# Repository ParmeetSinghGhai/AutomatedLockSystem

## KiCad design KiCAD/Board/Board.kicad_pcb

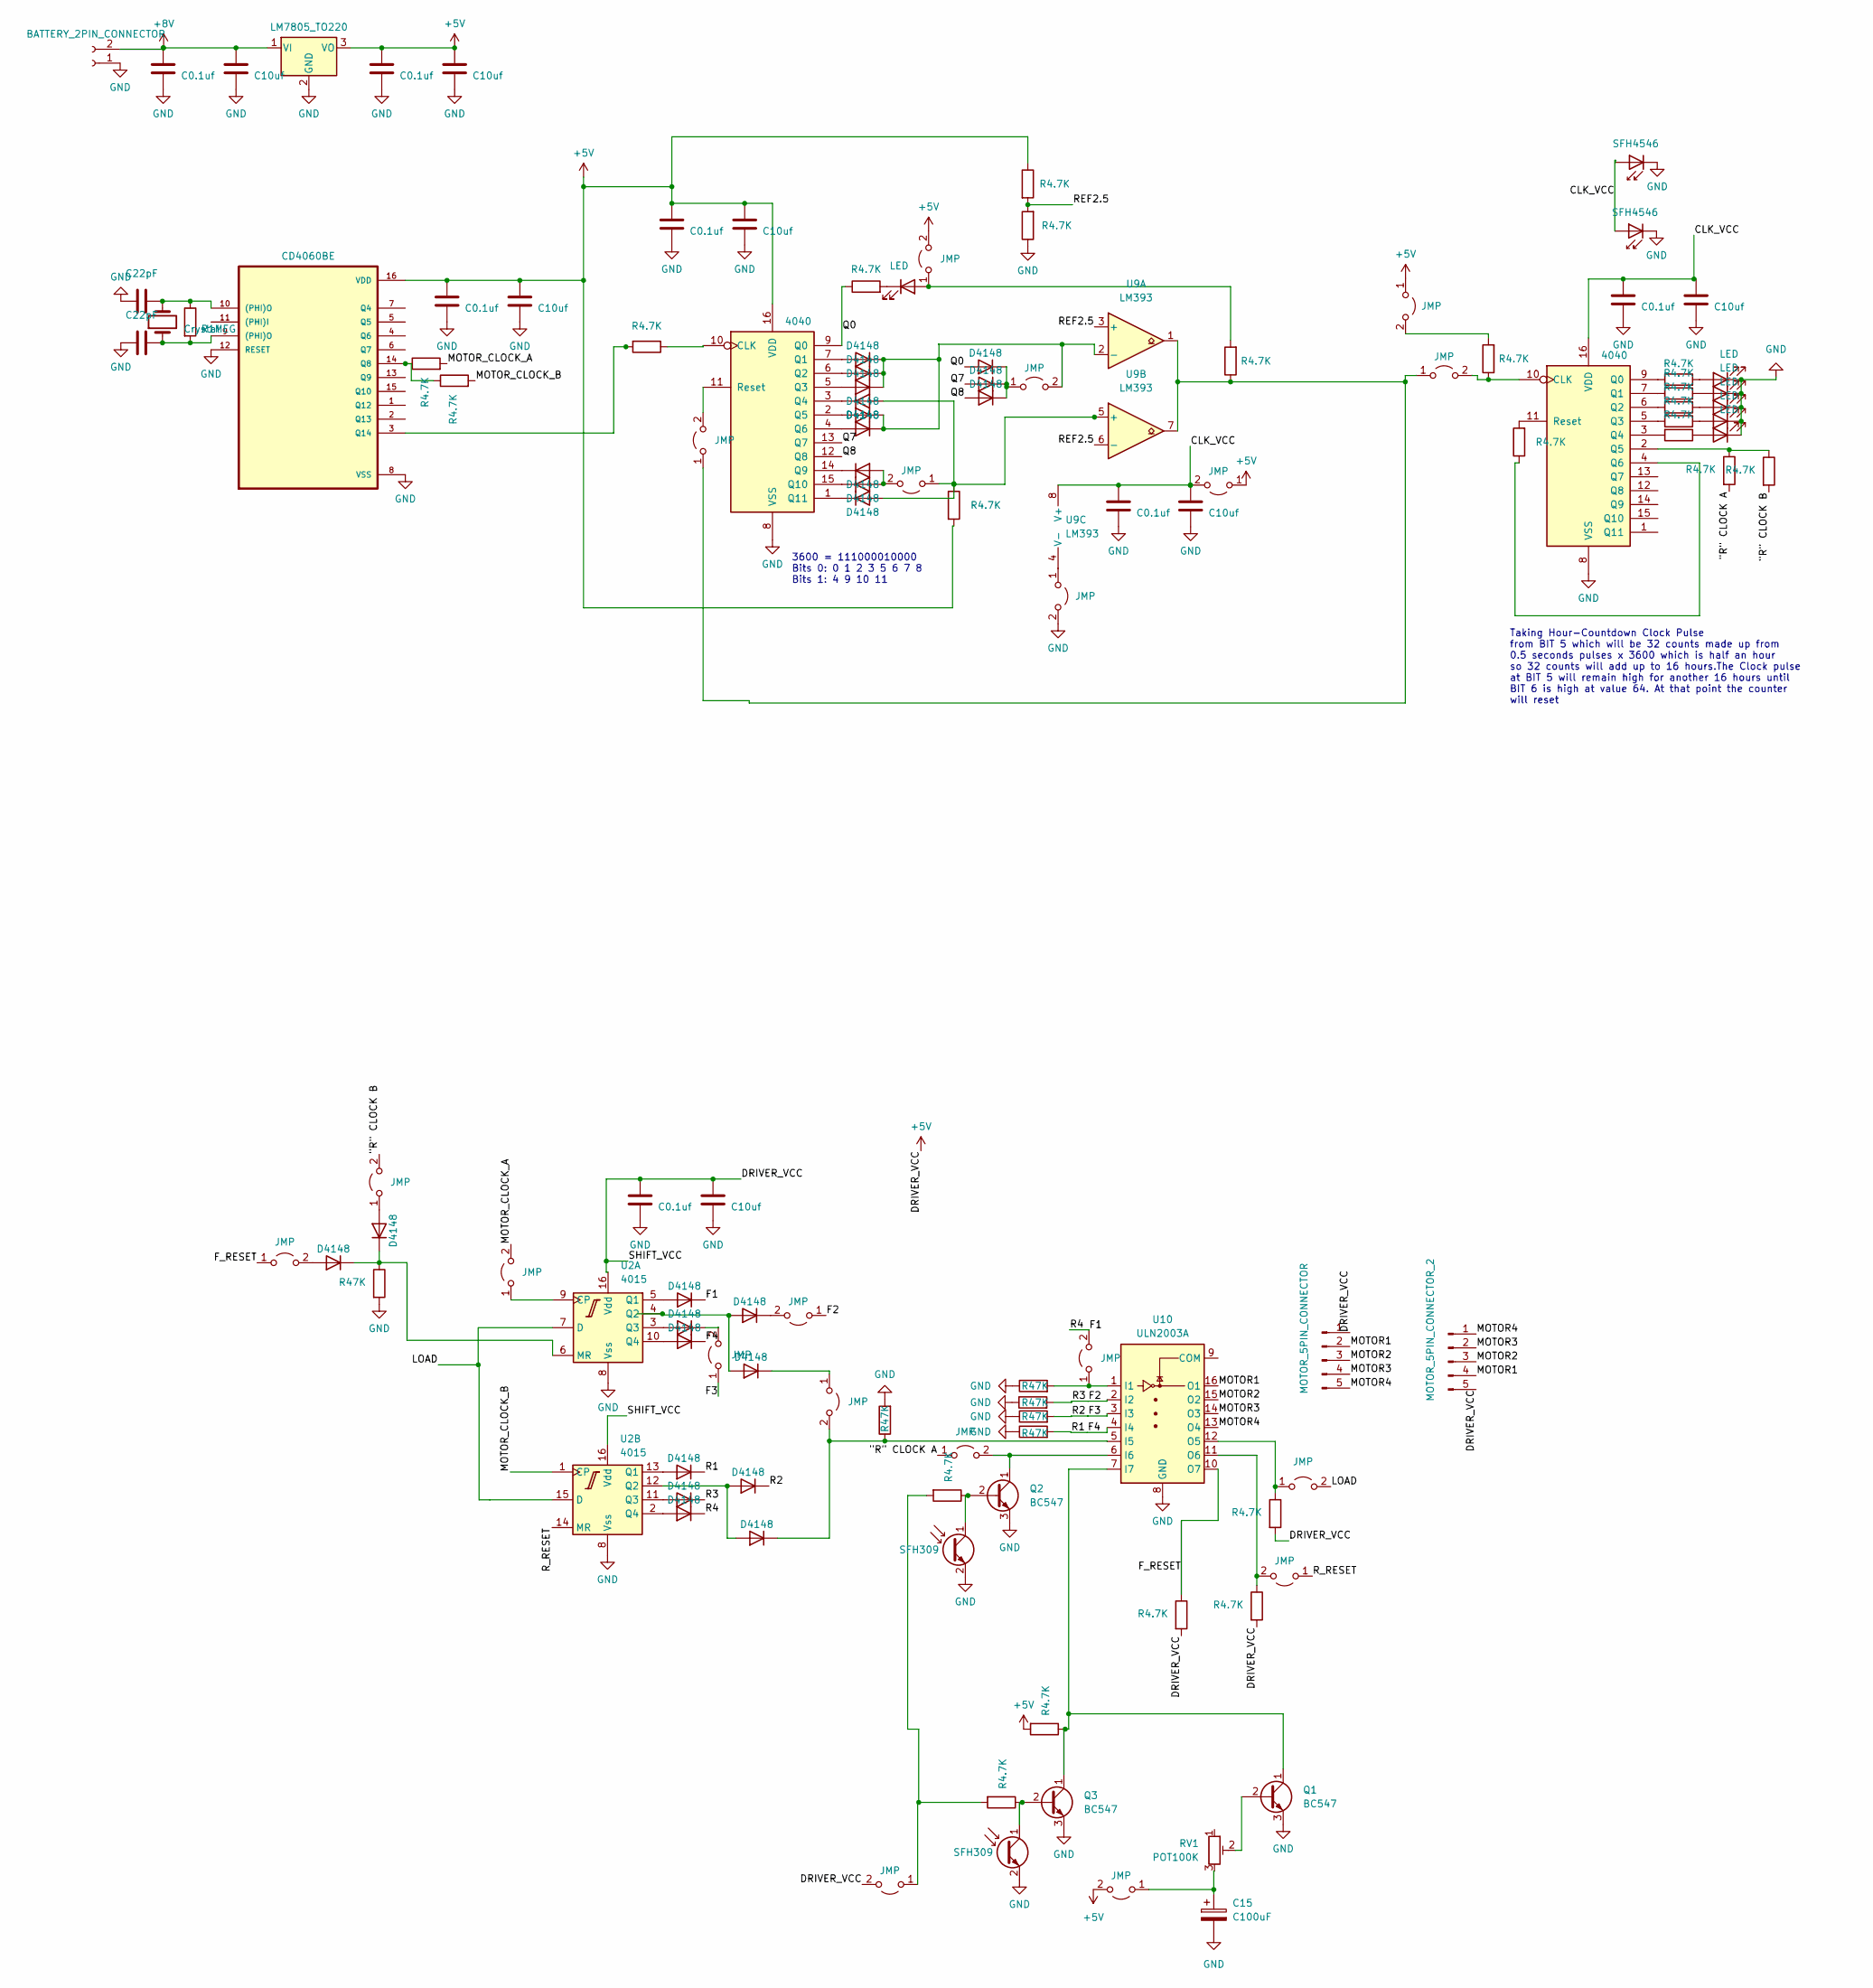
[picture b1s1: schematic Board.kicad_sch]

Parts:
C1, C4, C5, C7, C9, C11, C26: C0.1uf; C_Disc_D5.0mm_W2.5mm_P2.50mm
C2, C3, C6, C8, C10, C12, C27: C10uf; C_Radial_D6.3mm_H5.0mm_P2.50mm
C15: C100uF; CP_Radial_D10.0mm_P5.00mm
C24, C25: C22pF; C_Disc_D5.0mm_W2.5mm_P2.50mm
D1, D13: SFH4546; LED_D5.0mm_IRGrey
D2, D22, D23, D24, D25, D26: LED; LED_D3.0mm
D3, D4, D5, D6, D7, D8, D9, D10, D11, D12, D14, D15, D17, D18, D19, D20, D21, D27, D28, D29, D30, D31, D32, D33: D4148; D_DO-35_SOD27_P12.70mm_Horizontal
J1: MOTOR_5PIN_CONNECTOR; PinSocket_1x05_P2.54mm_Vertical
J2: MOTOR_5PIN_CONNECTOR_2; PinSocket_1x05_P2.54mm_Vertical
J3: BATTERY_2PIN_CONNECTOR; PinSocket_1x02_P2.54mm_Vertical
JP1, JP2, JP3, JP4, JP5, JP6, JP7, JP8, JP9, JP10, JP11, JP12, JP13, JP14, JP15, JP16, JP17, JP19, JP20, JP21: JMP; Jumper
Q1, Q2, Q3: BC547; TO-92_Inline
Q4, Q5: SFH309; LED_D3.0mm_Clear
R1, R2, R3, R4, R5, R7, R8, R9, R10, R11, R12, R13, R14, R15, R16, R17, R18, R21, R22, R23, R28, R29, R33: R4.7K; R_Axial_DIN0207_L6.3mm_D2.5mm_P10.16mm_Horizontal
R6: R1MEG; R_Axial_DIN0207_L6.3mm_D2.5mm_P10.16mm_Horizontal
R19, R20, R24, R25, R26, R27: R47K; R_Axial_DIN0207_L6.3mm_D2.5mm_P10.16mm_Horizontal
RV1: POT100K; Potentiometer_ACP_CA9-H3,8_Horizontal
U1, U5: 4040; DIP-16_W7.62mm_Socket
U2: 4015; DIP-16_W7.62mm_Socket
U8: LM7805_TO220; TO-220-3_Vertical
U9: LM393; DIP-8_W7.62mm_Socket
U10: ULN2003A; DIP-16_W7.62mm_Socket
U11: CD4060BE; DIP-16_W7.62mm_Socket
Y1: Crystal; Crystal_DS26_D2.0mm_L6.0mm_Vertical

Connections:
+5V: C5.1, C6.1, C7.1, C8.1, C11.1, C12.1, C26.1, C27.1, J1.1, J2.5, JP1.2 (B), JP6.1 (A), JP12.2 (B), JP19.2 (B), JP20.1 (A), R1.2, R4.1, R8.2, R13.2, R22.2, R23.2, U1.16 (VDD), U2.16 (Vdd), U8.3 (VO), U11.16 (VDD)
+8V: C3.1, C4.1, J3.2, U8.1 (VI)
/"R" CLOCK A: JP7.1 (A), R14.2
/"R" CLOCK B: JP8.2 (B), R2.2
/CLK_VCC: C1.1, C2.1, C9.1, C10.1, D1.2 (A), D13.2 (A), JP20.2 (B), U5.16 (VDD), U9.8 (V+)
/F1: D14.1 (K), D30.1 (K), JP15.2 (B)
/F2: D29.1 (K), JP17.1 (A), R24.2, U10.2 (I2)
/F3: D31.1 (K), JP16.1 (A), R25.2, U10.3 (I3)
/F4: D27.1 (K), D28.1 (K), R26.2, U10.4 (I4)
/F_RESET: JP14.1 (A), R22.1, U10.10 (O7)
/LOAD: JP9.2 (B), U2.7 (D), U2.15 (D)
/MOTOR1: J1.2, J2.4, U10.16 (O1)
/MOTOR2: J1.3, J2.3, U10.15 (O2)
/MOTOR3: J1.4, J2.2, U10.14 (O3)
/MOTOR4: J1.5, J2.1, U10.13 (O4)
/MOTOR_CLOCK_A: JP11.2 (B), R15.2
/MOTOR_CLOCK_B: R16.2, U2.1 (CP)
/Q0: D3.2 (A), R5.1, U1.9 (Q0)
/Q7: D9.2 (A), U1.13 (Q7)
/Q8: D10.2 (A), U1.12 (Q8)
/REF2.5: R4.2, R7.2, U9.3 (+), U9.6 (-)
/R_RESET: JP10.1 (A), U2.14 (MR)
GND: C1.2, C2.2, C3.2, C4.2, C5.2, C6.2, C7.2, C8.2, C9.2, C10.2, C11.2, C12.2, C15.2, C24.2, C25.2, C26.2, C27.2, D1.1 (K), D13.1 (K), D22.1 (K), D23.1 (K), D24.1 (K), D25.1 (K), D26.1 (K), J3.1, JP21.2 (B), Q1.3 (E), Q2.3 (E), Q3.3 (E), Q4.2 (E), Q5.2 (E), R7.1, R19.1, R20.2, R24.1, R25.1, R26.1, R27.2, U1.8 (VSS), U2.8 (Vss), U5.8 (VSS), U8.2 (GND), U10.8 (GND), U11.8 (VSS), U11.12 (RESET)
unnamed: C24.1, R6.1, U11.10 ((PHI)O), Y1.2
unnamed: C25.1, R6.2, U11.9 ((PHI)O), Y1.1
unnamed: D2.2 (A), JP19.1 (A), R9.2
unnamed: D2.1 (K), R5.2
unnamed: D4.2 (A), U1.7 (Q1)
unnamed: D4.1 (K), D5.1 (K), D6.1 (K), D7.1 (K), D8.1 (K), JP4.2 (B), U9.2 (-)
unnamed: D5.2 (A), U1.6 (Q2)
unnamed: D6.2 (A), U1.5 (Q3)
unnamed: D7.2 (A), U1.2 (Q5)
unnamed: D8.2 (A), U1.4 (Q6)
unnamed: D3.1 (K), D9.1 (K), D10.1 (K), JP4.1 (A)
unnamed: D11.2 (A), JP8.1 (A)
unnamed: D11.1 (K), D12.1 (K), R20.1, U2.6 (MR)
unnamed: D12.2 (A), JP14.2 (B)
unnamed: D14.2 (A), U2.5 (Q1)
unnamed: D15.2 (A), D33.2 (A), U2.4 (Q2)
unnamed: D15.1 (K), JP13.1 (A)
unnamed: D17.2 (A), U2.3 (Q3)
unnamed: D17.1 (K), JP16.2 (B)
unnamed: D18.2 (A), D21.2 (A), JP3.1 (A), R8.1, U9.5 (+)
unnamed: D18.1 (K), U1.1 (Q11)
unnamed: D19.2 (A), D20.2 (A), JP3.2 (B)
unnamed: D19.1 (K), U1.15 (Q10)
unnamed: D20.1 (K), U1.14 (Q9)
unnamed: D21.1 (K), U1.3 (Q4)
unnamed: D22.2 (A), R3.2
unnamed: D23.2 (A), R10.1
unnamed: D24.2 (A), R11.1
unnamed: D25.2 (A), R12.1
unnamed: D26.2 (A), R18.1
unnamed: D27.2 (A), U2.10 (Q4)
unnamed: D28.2 (A), U2.13 (Q1)
unnamed: D29.2 (A), U2.11 (Q3)
unnamed: D30.2 (A), U2.2 (Q4)
unnamed: D31.2 (A), D32.2 (A), U2.12 (Q2)
unnamed: D32.1 (K), JP13.2 (B), R27.1, U10.5 (I5)
unnamed: D33.1 (K), JP17.2 (B)
unnamed: C15.1, JP1.1 (A), RV1.3
unnamed: JP2.1 (A), JP5.1 (A), R9.1, U9.1, U9.7
unnamed: JP2.2 (B), U1.11 (Reset)
unnamed: JP5.2 (B), R17.1, U5.10 (CLK)
unnamed: JP6.2 (B), R17.2
unnamed: JP7.2 (B), Q2.1 (C), U10.6 (I6)
unnamed: JP9.1 (A), R1.1, U10.12 (O5)
unnamed: JP10.2 (B), R13.1, U10.11 (O6)
unnamed: JP11.1 (A), U2.9 (CP)
unnamed: JP12.1 (A), R28.2, R29.2
unnamed: JP15.1 (A), R19.2, U10.1 (I1)
unnamed: JP21.1 (A), U9.4 (V-)
unnamed: Q1.2 (B), RV1.2
unnamed: Q1.1 (C), Q3.1 (C), R23.1, U10.7 (I7)
unnamed: Q2.2 (B), Q5.1 (C), R28.1
unnamed: Q3.2 (B), Q4.1 (C), R29.1
unnamed: R33.1, U1.10 (CLK)
unnamed: R3.1, U5.9 (Q0)
unnamed: R10.2, U5.7 (Q1)
unnamed: R11.2, U5.6 (Q2)
unnamed: R12.2, U5.5 (Q3)
unnamed: R18.2, U5.3 (Q4)
unnamed: R2.1, R14.1, U5.2 (Q5)
unnamed: R21.1, U5.4 (Q6)
unnamed: R21.2, U5.11 (Reset)
unnamed: R15.1, R16.1, U11.14 (Q8)
unnamed: R33.2, U11.3 (Q14)

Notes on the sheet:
Taking Hour-Countdown Clock Pulse from BIT 5 which will be 32 counts made up from 0.5 seconds pulses x 3600 which is half an hour so 32 counts will add up to 16 hours.The Clock pulse at BIT 5 will remain high for another 16 hours until BIT 6 is high at value 64. At that point the counter will reset
3600 = 111000010000 Bits 0: 0 1 2 3 5 6 7 8 Bits 1: 4 9 10 11

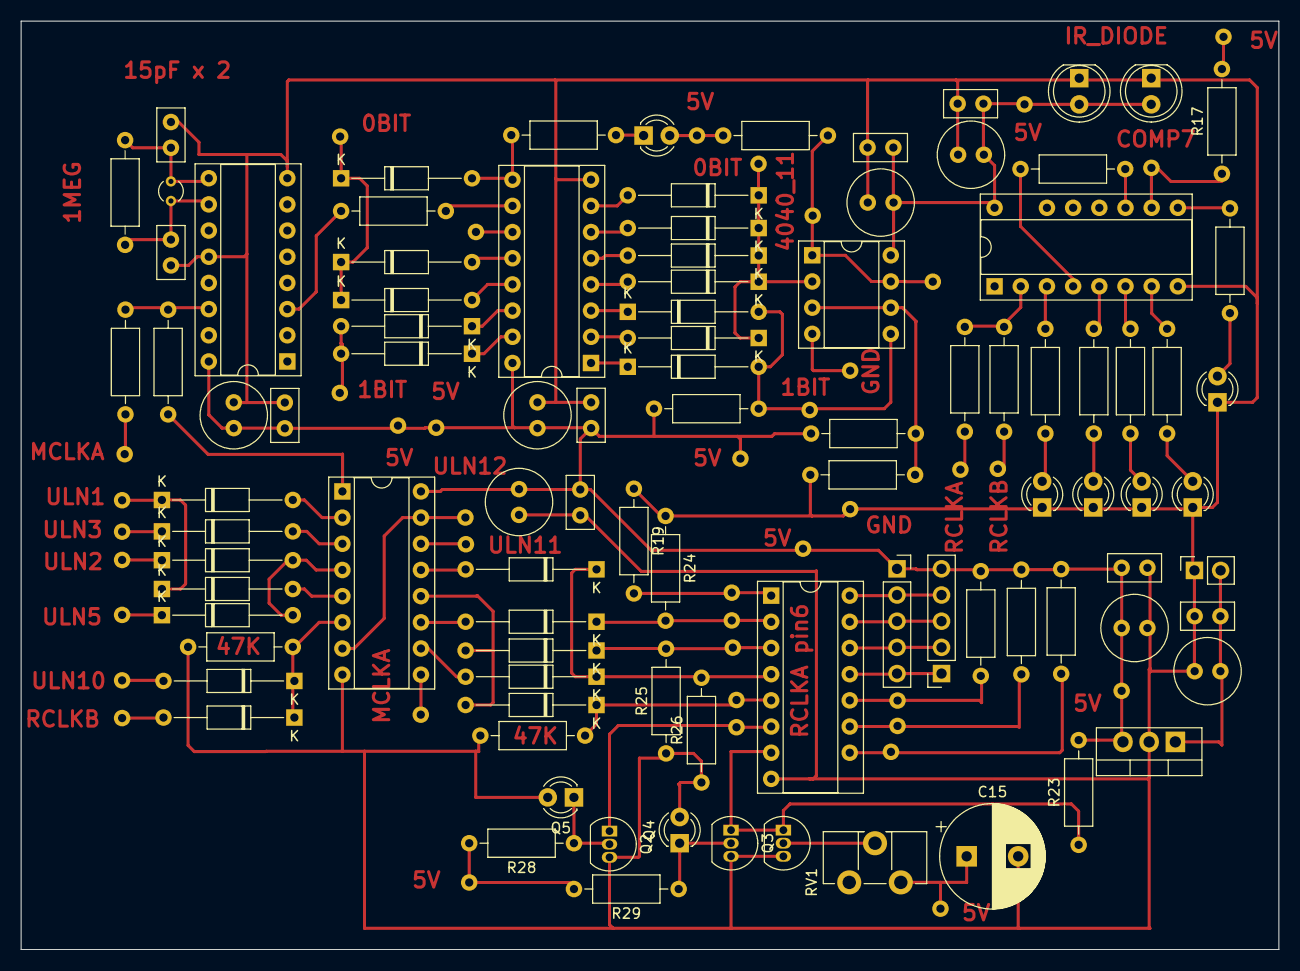
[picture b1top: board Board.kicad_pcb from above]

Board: 2 copper layers, 122.0 x 90.1 mm, 116 parts (0 on the bottom side), 87 nets.

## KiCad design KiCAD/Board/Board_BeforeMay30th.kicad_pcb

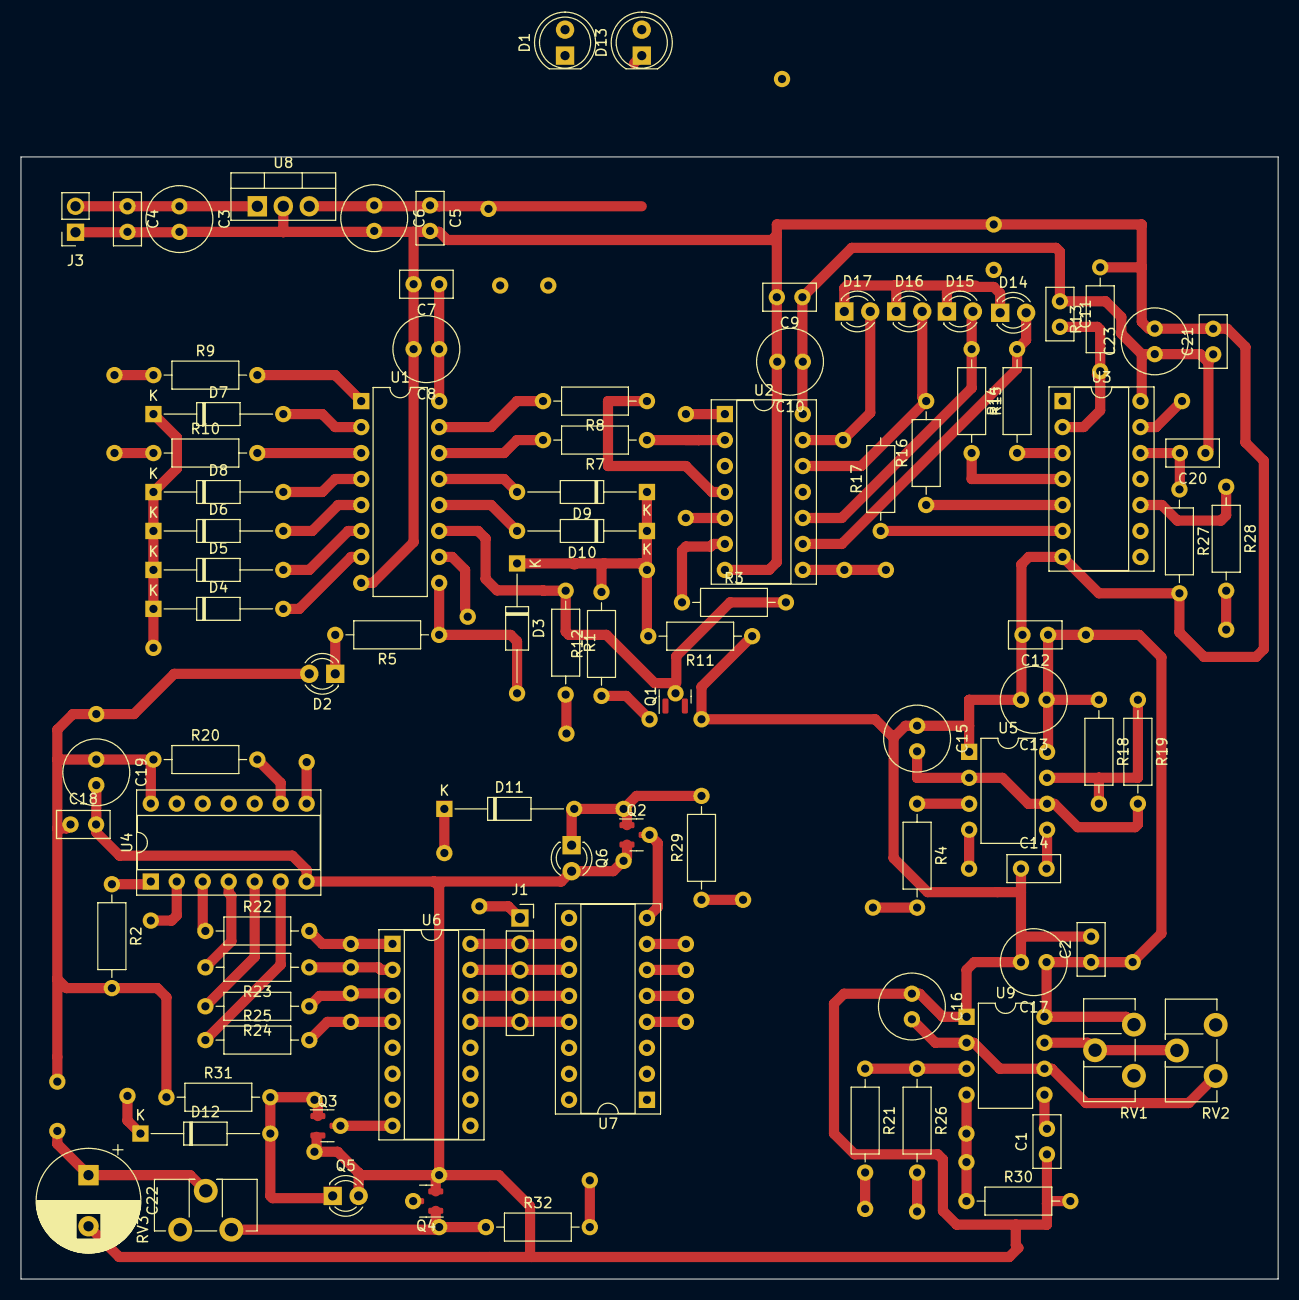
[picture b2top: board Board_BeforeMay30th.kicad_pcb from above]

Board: 2 copper layers, 122.9 x 109.7 mm, 117 parts (0 on the bottom side), 90 nets.

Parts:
C1, C2, C4, C5, C7, C9, C11, C12, C14, C18, C20, C21: C0.1uf; C_Disc_D5.0mm_W2.5mm_P2.50mm
C3, C6, C8, C10, C13, C15, C16, C17, C19, C23: C10uf; C_Radial_D6.3mm_H5.0mm_P2.50mm
C22: C100uf; CP_Radial_D10.0mm_P5.00mm
D1, D13: SFH4546; LED_D5.0mm_IRGrey
D2, D14, D15, D16, D17: LED; LED_D3.0mm
D3, D4, D5, D6, D7, D8, D9, D10, D11, D12: D4148; D_DO-35_SOD27_P12.70mm_Horizontal
J1: MOTOR_5PIN_CONNECTOR; PinSocket_1x05_P2.54mm_Vertical
J3: BATTERY_2PIN_CONNECTOR; PinSocket_1x02_P2.54mm_Vertical
JP1, JP2, JP3, JP4, JP5, JP6, JP7, JP8, JP9, JP10, JP11, JP12, JP13, JP14, JP15, JP16, JP17, JP18, JP19, JP20, JP21, JP23: JMP; Jumper
Q1, Q2, Q3, Q4: AO3400A; SOT-23
Q5, Q6: SFH309; LED_D3.0mm_Clear
R1, R2, R3, R4, R5, R7, R8, R9, R10, R12, R14, R15, R16, R17, R20, R21, R22, R23, R24, R25, R26, R28, R29, R31, R32: R4.7K; R_Axial_DIN0207_L6.3mm_D2.5mm_P10.16mm_Horizontal
R11, R13, R27, R30: R10K; R_Axial_DIN0207_L6.3mm_D2.5mm_P10.16mm_Horizontal
R18: R8.2K; R_Axial_DIN0207_L6.3mm_D2.5mm_P10.16mm_Horizontal
R19: R68K; R_Axial_DIN0207_L6.3mm_D2.5mm_P10.16mm_Horizontal
RV1, RV2, RV3: POT100K; Potentiometer_ACP_CA9-H3,8_Horizontal
SMD_2_DIP1, SMD_2_DIP2, SMD_2_DIP3, SMD_2_DIP4: SMD_2_DIP
U1: 4040; DIP-16_W7.62mm
U2: 7421; DIP-14_W7.62mm_Socket
U3: 74LS393; DIP-14_W7.62mm_Socket
U4: 74HC164; DIP-14_W7.62mm_Socket
U5, U9: NE555P; DIP-8_W7.62mm
U6, U7: ULN2003; DIP-16_W7.62mm_Socket
U8: LM7805_TO220; TO-220-3_Vertical

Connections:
+5V: C5.1, C6.1, C7.1, C8.1, C9.1, C10.1, C11.1, C20.1, C21.1, C23.1, D1.2 (A), D13.2 (A), JP6.2 (B), JP20.2 (B), JP21.2 (B), JP23.2 (B), U1.16 (VDD), U2.14 (VCC), U3.14 (VCC), U8.3 (VO)
+8V: C3.1, C4.1, J3.2, U8.1 (VI)
/7421_P1: JP5.1 (A), R10.1
/7421_P2: R7.1, U2.2
/7421_P4: R8.1, U2.4
/7421_P5: JP2.1 (A), R9.1
/ADHOC_LED_5V: C18.1, C19.1, D2.2 (A), JP8.1 (A), JP23.1 (A), R2.2, R20.1, R31.1, U4.14 (VCC)
/DIS_MOTOR: RV1.2, RV2.2, U9.7 (DIS)
/DIS_SYS: R18.2, R19.1, U5.7 (DIS)
/LOAD: JP9.1 (A), U4.2 (DSB)
/MOTOR1: J1.2, U6.16 (O1), U7.10 (O7)
/MOTOR2: J1.3, U6.15 (O2), U7.11 (O6)
/MOTOR3: J1.4, U6.14 (O3), U7.12 (O5)
/MOTOR4: J1.5, U6.13 (O4), U7.13 (O4)
/MOTOR_CLOCKA: JP16.2 (B), U4.8 (CP)
/MOTOR_CLOCKB: JP17.2 (B), U3.13 (CP)
/MOTOR_RESET: JP14.2 (B), JP15.1 (A), R30.1, U9.4 (R)
/REVERSE_MOTION: JP18.1 (A), JP19.2 (B), U2.8
/S0: JP13.2 (B), R22.2, U6.1 (I1)
/S1: JP12.2 (B), R23.1, U6.2 (I2)
/S2: JP11.2 (B), R24.1, U6.3 (I3)
/S3: JP10.2 (B), R25.2, U6.4 (I4)
/SYSTEM_CLOCK: JP3.2 (B), U1.10 (CLK)
/TRIG_MOTOR: C16.2, RV2.1, U9.2 (TR), U9.6 (THR)
/TRIG_SYS: C15.2, R19.2, U5.2 (TR), U5.6 (THR)
GND: C1.1, C2.2, C3.2, C4.2, C5.2, C6.2, C7.2, C8.2, C9.2, C10.2, C12.2, C13.2, C14.1, C15.1, C16.1, C17.2, C18.2, C19.2, C21.2, C22.2, C23.2, D1.1 (K), D13.1 (K), J3.1, JP7.2 (B), Q1.2 (S), Q2.2 (S), Q3.2 (S), Q4.2 (S), Q5.2 (E), Q6.2 (E), R11.1, R13.2, R27.2, R30.2, SMD_2_DIP1.2, SMD_2_DIP2.2, SMD_2_DIP3.2, SMD_2_DIP4.2, U1.8 (VSS), U2.7 (GND), U3.7 (GND), U4.7 (GND), U5.1 (GND), U8.2 (GND), U9.1 (GND)
unnamed: D2.1 (K), R5.2
unnamed: D3.2 (A), R5.1, U1.9 (Q0)
unnamed: D4.2 (A), U1.7 (Q1)
unnamed: D4.1 (K), D5.1 (K), D6.1 (K), D7.1 (K), D8.1 (K), JP1.1 (A)
unnamed: D5.2 (A), U1.6 (Q2)
unnamed: D6.2 (A), U1.5 (Q3)
unnamed: D7.2 (A), U1.2 (Q5)
unnamed: D8.2 (A), U1.4 (Q6)
unnamed: D9.2 (A), U1.13 (Q7)
unnamed: D10.2 (A), U1.12 (Q8)
unnamed: D3.1 (K), D9.1 (K), D10.1 (K), JP1.2 (B), R11.2, R12.2
unnamed: D11.2 (A), Q2.1 (G), Q6.1 (C), R29.2, SMD_2_DIP2.1
unnamed: D11.1 (K), JP15.2 (B)
unnamed: D12.2 (A), Q3.1 (G), Q4.3 (D), Q5.1 (C), R31.2, SMD_2_DIP3.1, SMD_2_DIP4.3
unnamed: D12.1 (K), JP14.1 (A)
unnamed: D14.2 (A), R14.2, U2.9
unnamed: D14.1 (K), D15.1 (K), D16.1 (K), D17.1 (K), JP7.1 (A)
unnamed: D15.2 (A), R15.1, U2.10
unnamed: D16.2 (A), R16.2, U2.12
unnamed: D17.2 (A), R17.2, U2.13
unnamed: J1.1, JP20.1 (A)
unnamed: JP2.2 (B), U2.5
unnamed: JP3.1 (A), R4.2
unnamed: JP4.2 (B), U5.4 (R)
unnamed: JP5.2 (B), U2.1
unnamed: JP6.1 (A), R1.2
unnamed: C22.1, JP8.2 (B), RV3.2
unnamed: JP9.2 (B), R28.2
unnamed: JP10.1 (A), U7.7 (I7)
unnamed: JP11.1 (A), U7.6 (I6)
unnamed: JP12.1 (A), U7.5 (I5)
unnamed: JP13.1 (A), U7.4 (I4)
unnamed: JP16.1 (A), R21.2
unnamed: JP17.1 (A), R26.2
unnamed: JP18.2 (B), R32.2
unnamed: JP19.1 (A), R29.1
unnamed: C2.1, C12.1, C13.1, C17.1, JP4.1 (A), JP21.1 (A), R18.1, RV1.3, U5.8 (VCC), U9.8 (VCC)
unnamed: Q1.3 (D), R1.1, R3.2, SMD_2_DIP1.3, U1.11 (Reset), U3.1 (CP)
unnamed: Q1.1 (G), R12.1, SMD_2_DIP1.1
unnamed: Q2.3 (D), SMD_2_DIP2.3, U7.8 (GND)
unnamed: Q3.3 (D), SMD_2_DIP3.3, U6.8 (GND)
unnamed: Q4.1 (G), R32.1, RV3.3, SMD_2_DIP4.1
unnamed: R3.1, U2.6
unnamed: R10.2, U1.3 (Q4)
unnamed: R7.2, U1.14 (Q9)
unnamed: R8.2, U1.15 (Q10)
unnamed: R9.2, U1.1 (Q11)
unnamed: C11.2, R13.1, U3.2 (MR)
unnamed: R14.1, U3.3 (Q0)
unnamed: R15.2, U3.4 (Q1)
unnamed: R16.1, U3.5 (Q2)
unnamed: R17.1, U3.6 (Q3)
unnamed: C20.2, R27.1, U3.12 (MR)
unnamed: R28.1, U3.10 (Q1)
unnamed: R2.1, U4.1 (DSA)
unnamed: R22.1, U4.3 (Q0)
unnamed: R23.2, U4.4 (Q1)
unnamed: R24.2, U4.5 (Q2)
unnamed: R25.1, U4.6 (Q3)
unnamed: R20.2, U4.9 (~MR)
unnamed: C14.2, U5.5 (CV)
unnamed: R4.1, U5.3 (Q)
unnamed: C1.2, U9.5 (CV)
unnamed: R21.1, R26.1, U9.3 (Q)

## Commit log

2025-05-25 Updated 25th May 2025 11:50AM IST
2025-05-25 Updated on 25th May 2025 16:06 _4:06PM IST
2025-05-25 Added Rough Design On Papper
2025-05-25 opentimeStamps.org Till 25thMay2025
2025-05-27 May27th Update
    dropped the idea of using mosfets for comparing bits of CD4040 due to logic level instability.
    using 74HC21 AND gate chip for comparing 4 one's bits of CD4040 and 4 one's bits of 74HC393
2025-05-28 Updated on May28th2025
    Added KiCAD Board
2025-05-29 Updated On May 29th 2025
    KiCAD Board Almost Done. Will require minor touch ups tomm.
2025-05-30 Updated on May 30th 2025
    Greatly reduced component count and simplified the design and logic of the circuit.
    help definitely help with soldering
2025-05-31 May 31st 2025 Updated
    Major Design Changed. using LM393 instead of 74HC21 to get half an hour clock signal into hour counter.
    connections are more streamlined and easy to solder. Less components as well. went down from 5 mosfets to now just 2 and chips are 6 in total
2025-06-01 June 1st Updated
    Greatly simplified design using ULN2003 completely and all of its pins. down to only 6 chips and 1 mosfet !!! . This will be the last design modification. its perfect at this point
2025-06-01 June 1st Project COMPLETED
    Project Completed and Ready for Soldering
2025-06-03 June 3rd 2025 Update
    Added ULN2003 Pull down Resistors for Stepper Motor Control
2025-06-10 10th June 2025 Updated
    Added Pull Downs 47K to ULN2003. Inverted Logic for Photo Transistors where cutting off IR rays off of photo transistors turns off forward and reverse motion since blocking IR rays is easier then ref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
